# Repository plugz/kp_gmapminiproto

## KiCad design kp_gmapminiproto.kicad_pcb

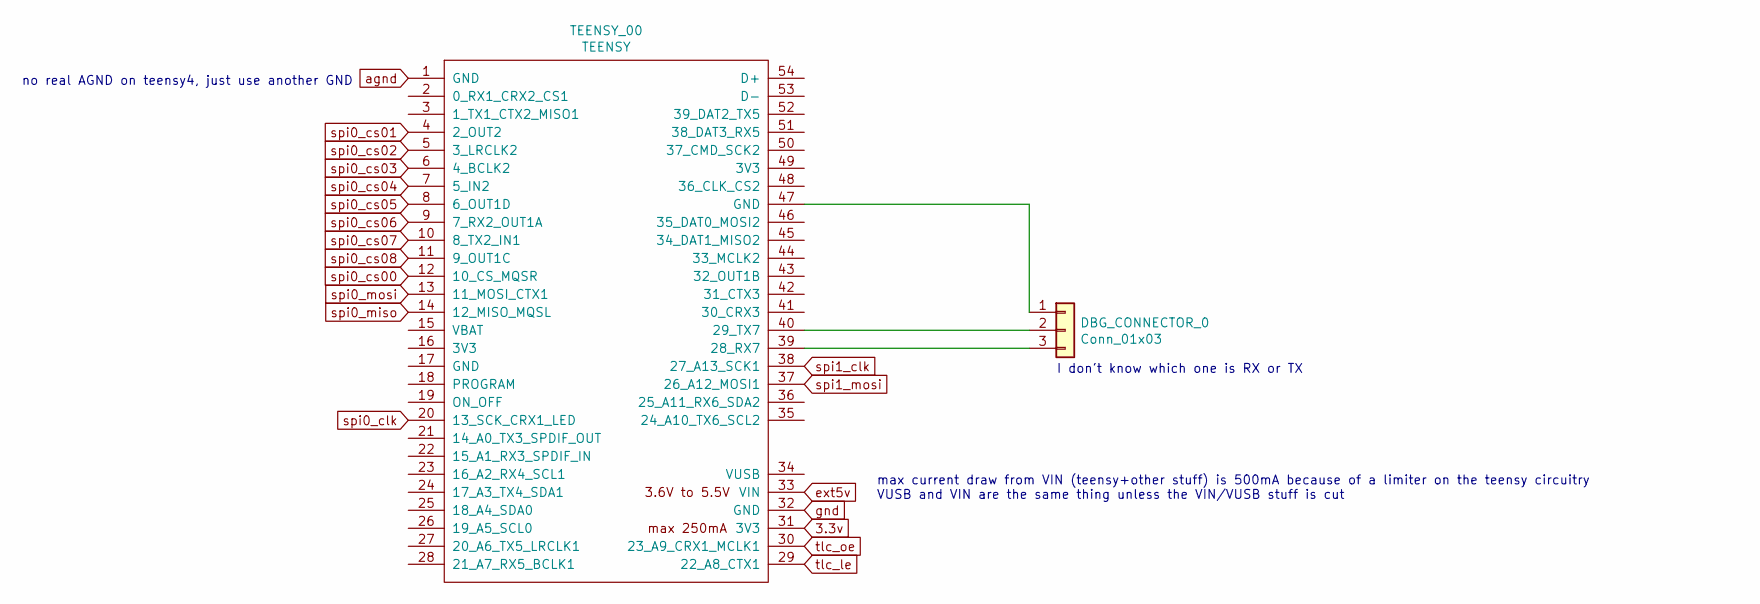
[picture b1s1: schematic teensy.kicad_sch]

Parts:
DBG_CONNECTOR_0: Conn_01x03; PinSocket_1x03_P2.54mm_Vertical
TEENSY_00: TEENSY; Teensy40_SMT

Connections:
3.3v: TEENSY_00.31 (3V3); also elsewhere on the board
unnamed: DBG_CONNECTOR_0.1, TEENSY_00.47 (GND)
unnamed: DBG_CONNECTOR_0.2, TEENSY_00.40 (29_TX7)
unnamed: DBG_CONNECTOR_0.3, TEENSY_00.39 (28_RX7)
agnd: TEENSY_00.1 (GND); also elsewhere on the board
ext5v: TEENSY_00.33 (VIN); also elsewhere on the board
gnd: TEENSY_00.32 (GND); also elsewhere on the board
spi0_clk: TEENSY_00.20 (13_SCK_CRX1_LED); also elsewhere on the board
spi0_cs00: TEENSY_00.12 (10_CS_MQSR); also elsewhere on the board
spi0_cs01: TEENSY_00.4 (2_OUT2); also elsewhere on the board
spi0_cs02: TEENSY_00.5 (3_LRCLK2); also elsewhere on the board
spi0_cs03: TEENSY_00.6 (4_BCLK2); also elsewhere on the board
spi0_cs04: TEENSY_00.7 (5_IN2); also elsewhere on the board
spi0_cs05: TEENSY_00.8 (6_OUT1D); also elsewhere on the board
spi0_cs06: TEENSY_00.9 (7_RX2_OUT1A); also elsewhere on the board
spi0_cs07: TEENSY_00.10 (8_TX2_IN1); also elsewhere on the board
spi0_cs08: TEENSY_00.11 (9_OUT1C); also elsewhere on the board
spi0_miso: TEENSY_00.14 (12_MISO_MQSL); also elsewhere on the board
spi0_mosi: TEENSY_00.13 (11_MOSI_CTX1); also elsewhere on the board
spi1_clk: TEENSY_00.38 (27_A13_SCK1); also elsewhere on the board
spi1_mosi: TEENSY_00.37 (26_A12_MOSI1); also elsewhere on the board
tlc_le: TEENSY_00.29 (22_A8_CTX1); also elsewhere on the board
tlc_oe: TEENSY_00.30 (23_A9_CRX1_MCLK1); also elsewhere on the board

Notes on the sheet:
max current draw from VIN (teensy+other stuff) is 500mA because of a limiter on the teensy circuitry VUSB and VIN are the same thing unless the VIN/VUSB stuff is cut
I don't know which one is RX or TX
no real AGND on teensy4, just use another GND

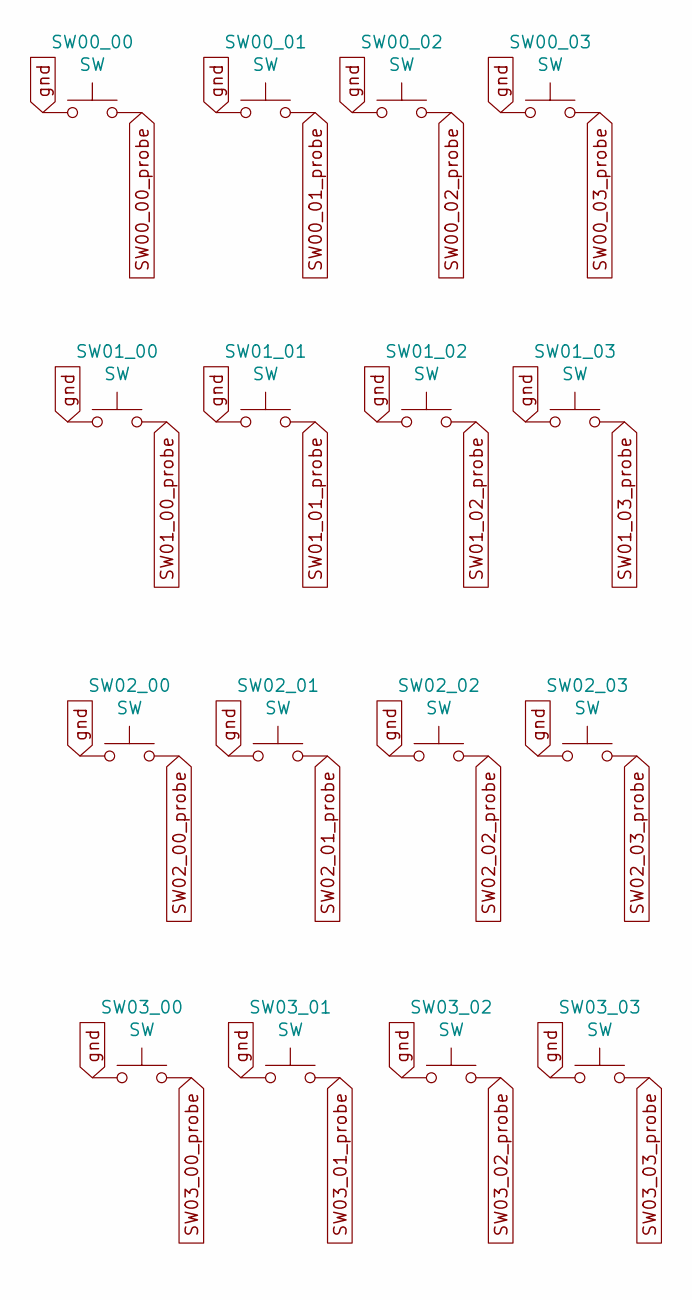
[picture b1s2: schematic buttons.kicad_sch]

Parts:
SW00_00, SW00_01, SW00_02, SW00_03, SW01_00, SW01_01, SW01_02, SW01_03, SW02_00, SW02_01, SW02_02, SW02_03, SW03_00, SW03_01, SW03_02, SW03_03: SW; SW_PUSH_6mm_h9.5mm

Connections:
SW00_00_probe: SW00_00.2; also elsewhere on the board
SW00_01_probe: SW00_01.2; also elsewhere on the board
SW00_02_probe: SW00_02.2; also elsewhere on the board
SW00_03_probe: SW00_03.2; also elsewhere on the board
SW01_00_probe: SW01_00.2; also elsewhere on the board
SW01_01_probe: SW01_01.2; also elsewhere on the board
SW01_02_probe: SW01_02.2; also elsewhere on the board
SW01_03_probe: SW01_03.2; also elsewhere on the board
SW02_00_probe: SW02_00.2; also elsewhere on the board
SW02_01_probe: SW02_01.2; also elsewhere on the board
SW02_02_probe: SW02_02.2; also elsewhere on the board
SW02_03_probe: SW02_03.2; also elsewhere on the board
SW03_00_probe: SW03_00.2; also elsewhere on the board
SW03_01_probe: SW03_01.2; also elsewhere on the board
SW03_02_probe: SW03_02.2; also elsewhere on the board
SW03_03_probe: SW03_03.2; also elsewhere on the board
gnd: SW00_00.1, SW00_01.1, SW00_02.1, SW00_03.1, SW01_00.1, SW01_01.1, SW01_02.1, SW01_03.1, SW02_00.1, SW02_01.1, SW02_02.1, SW02_03.1, SW03_00.1, SW03_01.1, SW03_02.1, SW03_03.1; also elsewhere on the board

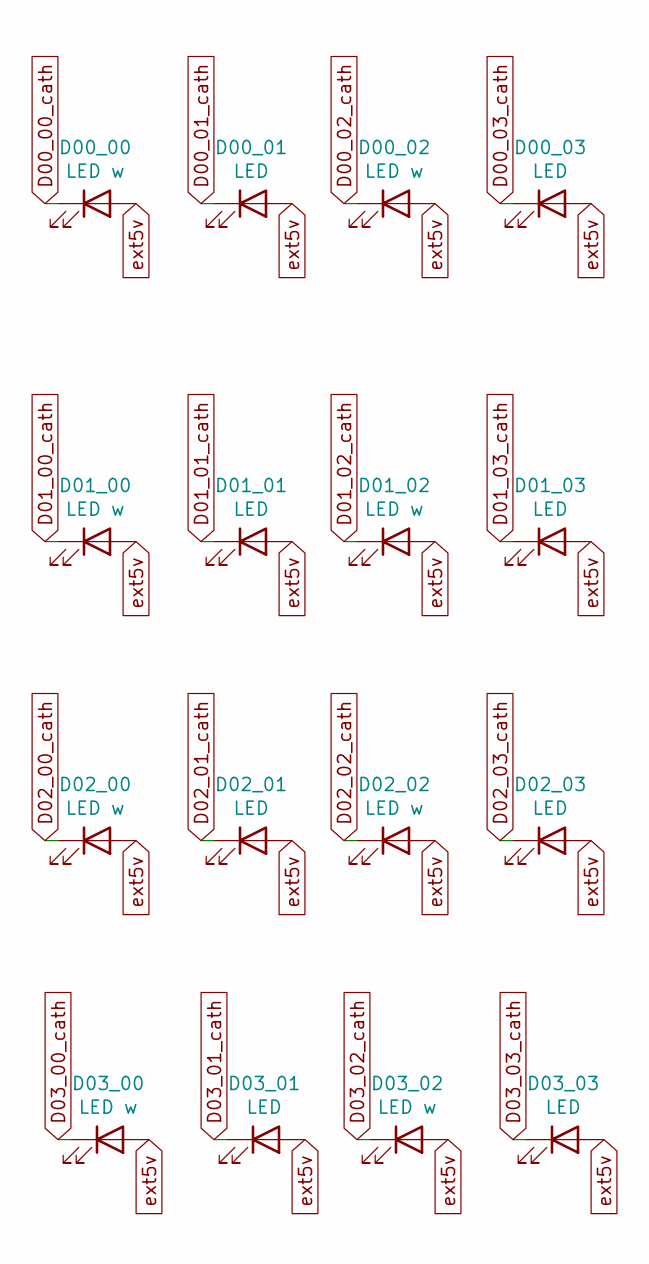
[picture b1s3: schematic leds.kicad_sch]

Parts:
D00_00, D00_02, D01_00, D01_02, D02_00, D02_02, D03_00, D03_02: LED w; LED_D3.0mm
D00_01, D00_03, D01_01, D01_03, D02_01, D02_03, D03_01, D03_03: LED; LED_D3.0mm

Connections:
D00_00_cath: D00_00.1 (K); also elsewhere on the board
D00_01_cath: D00_01.1 (K); also elsewhere on the board
D00_02_cath: D00_02.1 (K); also elsewhere on the board
D00_03_cath: D00_03.1 (K); also elsewhere on the board
D01_00_cath: D01_00.1 (K); also elsewhere on the board
D01_01_cath: D01_01.1 (K); also elsewhere on the board
D01_02_cath: D01_02.1 (K); also elsewhere on the board
D01_03_cath: D01_03.1 (K); also elsewhere on the board
D02_00_cath: D02_00.1 (K); also elsewhere on the board
D02_01_cath: D02_01.1 (K); also elsewhere on the board
D02_02_cath: D02_02.1 (K); also elsewhere on the board
D02_03_cath: D02_03.1 (K); also elsewhere on the board
D03_00_cath: D03_00.1 (K); also elsewhere on the board
D03_01_cath: D03_01.1 (K); also elsewhere on the board
D03_02_cath: D03_02.1 (K); also elsewhere on the board
D03_03_cath: D03_03.1 (K); also elsewhere on the board
ext5v: D00_00.2 (A), D00_01.2 (A), D00_02.2 (A), D00_03.2 (A), D01_00.2 (A), D01_01.2 (A), D01_02.2 (A), D01_03.2 (A), D02_00.2 (A), D02_01.2 (A), D02_02.2 (A), D02_03.2 (A), D03_00.2 (A), D03_01.2 (A), D03_02.2 (A), D03_03.2 (A); also elsewhere on the board

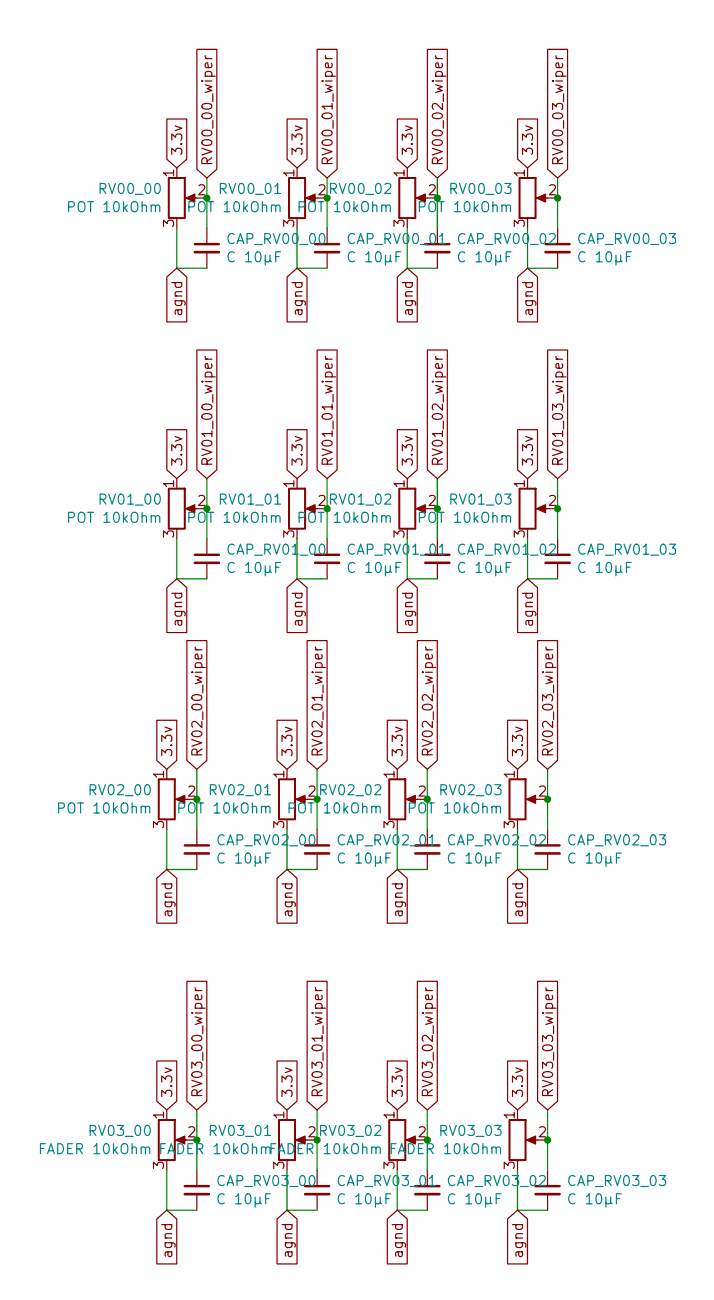
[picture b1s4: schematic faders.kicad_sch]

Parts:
CAP_RV00_00, CAP_RV00_01, CAP_RV00_02, CAP_RV00_03, CAP_RV01_00, CAP_RV01_01, CAP_RV01_02, CAP_RV01_03, CAP_RV02_00, CAP_RV02_01, CAP_RV02_02, CAP_RV02_03, CAP_RV03_00, CAP_RV03_01, CAP_RV03_02, CAP_RV03_03: C 10µF; C_Disc_D5.0mm_W2.5mm_P2.50mm
RV00_00, RV00_01, RV00_02, RV00_03, RV01_00, RV01_01, RV01_02, RV01_03, RV02_00, RV02_01, RV02_02, RV02_03: POT 10kOhm; Potentiometer_Alps_RK09K_Horizontal
RV03_00, RV03_01, RV03_02, RV03_03: FADER 10kOhm; Potentiometer_Bourns_PTA6043_Single_Slide

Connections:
3.3v: RV00_00.1, RV00_01.1, RV00_02.1, RV00_03.1, RV01_00.1, RV01_01.1, RV01_02.1, RV01_03.1, RV02_00.1, RV02_01.1, RV02_02.1, RV02_03.1, RV03_00.1, RV03_01.1, RV03_02.1, RV03_03.1; also elsewhere on the board
RV00_00_wiper: CAP_RV00_00.1, RV00_00.2; also elsewhere on the board
RV00_01_wiper: CAP_RV00_01.1, RV00_01.2; also elsewhere on the board
RV00_02_wiper: CAP_RV00_02.1, RV00_02.2; also elsewhere on the board
RV00_03_wiper: CAP_RV00_03.1, RV00_03.2; also elsewhere on the board
RV01_00_wiper: CAP_RV01_00.1, RV01_00.2; also elsewhere on the board
RV01_01_wiper: CAP_RV01_01.1, RV01_01.2; also elsewhere on the board
RV01_02_wiper: CAP_RV01_02.1, RV01_02.2; also elsewhere on the board
RV01_03_wiper: CAP_RV01_03.1, RV01_03.2; also elsewhere on the board
RV02_00_wiper: CAP_RV02_00.1, RV02_00.2; also elsewhere on the board
RV02_01_wiper: CAP_RV02_01.1, RV02_01.2; also elsewhere on the board
RV02_02_wiper: CAP_RV02_02.1, RV02_02.2; also elsewhere on the board
RV02_03_wiper: CAP_RV02_03.1, RV02_03.2; also elsewhere on the board
RV03_00_wiper: CAP_RV03_00.1, RV03_00.2; also elsewhere on the board
RV03_01_wiper: CAP_RV03_01.1, RV03_01.2; also elsewhere on the board
RV03_02_wiper: CAP_RV03_02.1, RV03_02.2; also elsewhere on the board
RV03_03_wiper: CAP_RV03_03.1, RV03_03.2; also elsewhere on the board
agnd: CAP_RV00_00.2, CAP_RV00_01.2, CAP_RV00_02.2, CAP_RV00_03.2, CAP_RV01_00.2, CAP_RV01_01.2, CAP_RV01_02.2, CAP_RV01_03.2, CAP_RV02_00.2, CAP_RV02_01.2, CAP_RV02_02.2, CAP_RV02_03.2, CAP_RV03_00.2, CAP_RV03_01.2, CAP_RV03_02.2, CAP_RV03_03.2, RV00_00.3, RV00_01.3, RV00_02.3, RV00_03.3, RV01_00.3, RV01_01.3, RV01_02.3, RV01_03.3, RV02_00.3, RV02_01.3, RV02_02.3, RV02_03.3, RV03_00.3, RV03_01.3, RV03_02.3, RV03_03.3; also elsewhere on the board

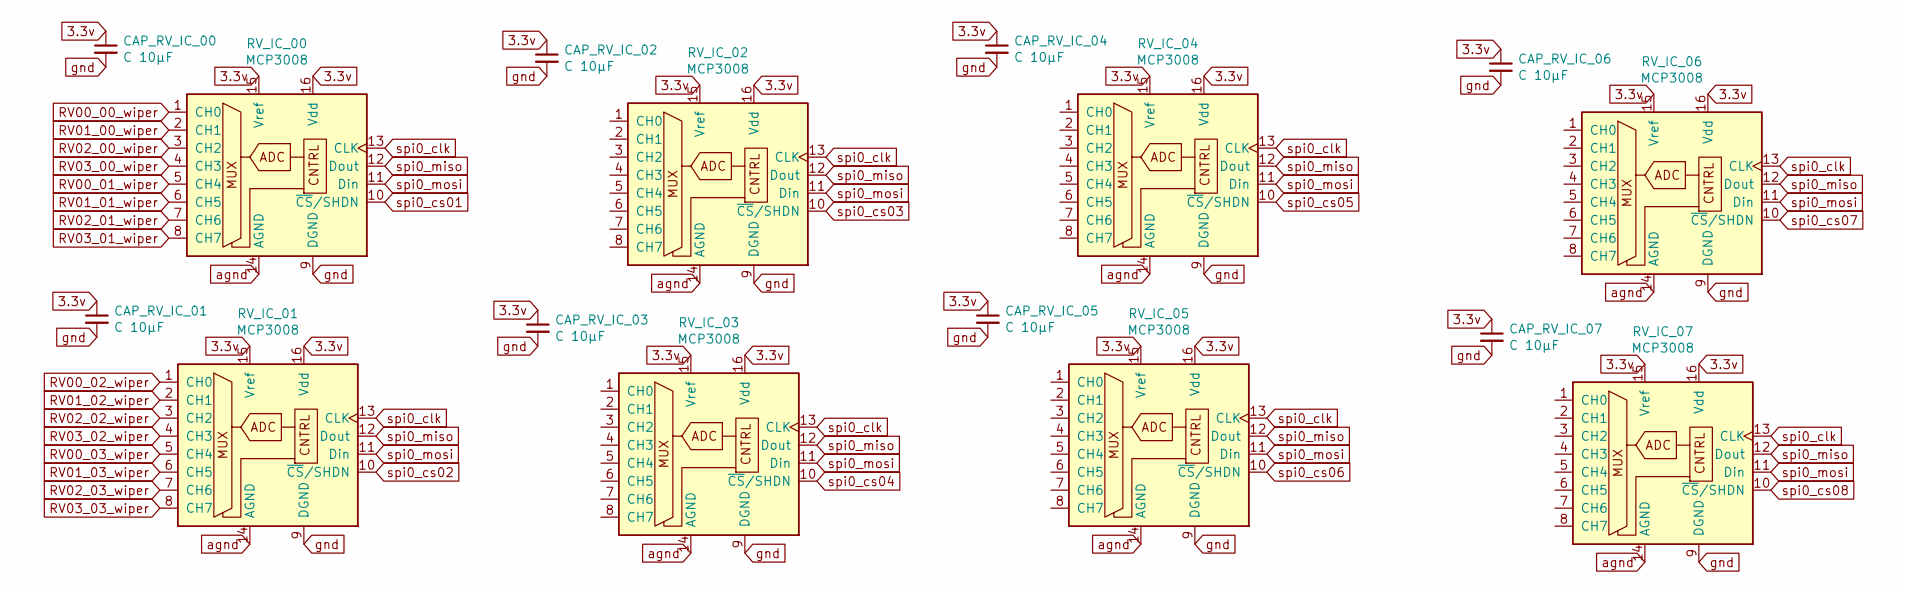
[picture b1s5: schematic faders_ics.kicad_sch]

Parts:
CAP_RV_IC_00, CAP_RV_IC_01, CAP_RV_IC_02, CAP_RV_IC_03, CAP_RV_IC_04, CAP_RV_IC_05, CAP_RV_IC_06, CAP_RV_IC_07: C 10µF; C_Disc_D5.0mm_W2.5mm_P2.50mm
RV_IC_00, RV_IC_01, RV_IC_02, RV_IC_03, RV_IC_04, RV_IC_05, RV_IC_06, RV_IC_07: MCP3008; DIP-16_W7.62mm

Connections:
3.3v: CAP_RV_IC_00.1, CAP_RV_IC_01.1, CAP_RV_IC_02.1, CAP_RV_IC_03.1, CAP_RV_IC_04.1, CAP_RV_IC_05.1, CAP_RV_IC_06.1, CAP_RV_IC_07.1, RV_IC_00.15 (Vref), RV_IC_00.16 (Vdd), RV_IC_01.15 (Vref), RV_IC_01.16 (Vdd), RV_IC_02.15 (Vref), RV_IC_02.16 (Vdd), RV_IC_03.15 (Vref), RV_IC_03.16 (Vdd), RV_IC_04.15 (Vref), RV_IC_04.16 (Vdd), RV_IC_05.15 (Vref), RV_IC_05.16 (Vdd), RV_IC_06.15 (Vref), RV_IC_06.16 (Vdd), RV_IC_07.15 (Vref), RV_IC_07.16 (Vdd); also elsewhere on the board
RV00_00_wiper: RV_IC_00.1 (CH0); also elsewhere on the board
RV00_01_wiper: RV_IC_00.5 (CH4); also elsewhere on the board
RV00_02_wiper: RV_IC_01.1 (CH0); also elsewhere on the board
RV00_03_wiper: RV_IC_01.5 (CH4); also elsewhere on the board
RV01_00_wiper: RV_IC_00.2 (CH1); also elsewhere on the board
RV01_01_wiper: RV_IC_00.6 (CH5); also elsewhere on the board
RV01_02_wiper: RV_IC_01.2 (CH1); also elsewhere on the board
RV01_03_wiper: RV_IC_01.6 (CH5); also elsewhere on the board
RV02_00_wiper: RV_IC_00.3 (CH2); also elsewhere on the board
RV02_01_wiper: RV_IC_00.7 (CH6); also elsewhere on the board
RV02_02_wiper: RV_IC_01.3 (CH2); also elsewhere on the board
RV02_03_wiper: RV_IC_01.7 (CH6); also elsewhere on the board
RV03_00_wiper: RV_IC_00.4 (CH3); also elsewhere on the board
RV03_01_wiper: RV_IC_00.8 (CH7); also elsewhere on the board
RV03_02_wiper: RV_IC_01.4 (CH3); also elsewhere on the board
RV03_03_wiper: RV_IC_01.8 (CH7); also elsewhere on the board
agnd: RV_IC_00.14 (AGND), RV_IC_01.14 (AGND), RV_IC_02.14 (AGND), RV_IC_03.14 (AGND), RV_IC_04.14 (AGND), RV_IC_05.14 (AGND), RV_IC_06.14 (AGND), RV_IC_07.14 (AGND); also elsewhere on the board
gnd: CAP_RV_IC_00.2, CAP_RV_IC_01.2, CAP_RV_IC_02.2, CAP_RV_IC_03.2, CAP_RV_IC_04.2, CAP_RV_IC_05.2, CAP_RV_IC_06.2, CAP_RV_IC_07.2, RV_IC_00.9 (DGND), RV_IC_01.9 (DGND), RV_IC_02.9 (DGND), RV_IC_03.9 (DGND), RV_IC_04.9 (DGND), RV_IC_05.9 (DGND), RV_IC_06.9 (DGND), RV_IC_07.9 (DGND); also elsewhere on the board
spi0_clk: RV_IC_00.13 (CLK), RV_IC_01.13 (CLK), RV_IC_02.13 (CLK), RV_IC_03.13 (CLK), RV_IC_04.13 (CLK), RV_IC_05.13 (CLK), RV_IC_06.13 (CLK), RV_IC_07.13 (CLK); also elsewhere on the board
spi0_cs01: RV_IC_00.10 (~CS/SHDN); also elsewhere on the board
spi0_cs02: RV_IC_01.10 (~CS/SHDN); also elsewhere on the board
spi0_cs03: RV_IC_02.10 (~CS/SHDN); also elsewhere on the board
spi0_cs04: RV_IC_03.10 (~CS/SHDN); also elsewhere on the board
spi0_cs05: RV_IC_04.10 (~CS/SHDN); also elsewhere on the board
spi0_cs06: RV_IC_05.10 (~CS/SHDN); also elsewhere on the board
spi0_cs07: RV_IC_06.10 (~CS/SHDN); also elsewhere on the board
spi0_cs08: RV_IC_07.10 (~CS/SHDN); also elsewhere on the board
spi0_miso: RV_IC_00.12 (Dout), RV_IC_01.12 (Dout), RV_IC_02.12 (Dout), RV_IC_03.12 (Dout), RV_IC_04.12 (Dout), RV_IC_05.12 (Dout), RV_IC_06.12 (Dout), RV_IC_07.12 (Dout); also elsewhere on the board
spi0_mosi: RV_IC_00.11 (Din), RV_IC_01.11 (Din), RV_IC_02.11 (Din), RV_IC_03.11 (Din), RV_IC_04.11 (Din), RV_IC_05.11 (Din), RV_IC_06.11 (Din), RV_IC_07.11 (Din); also elsewhere on the board

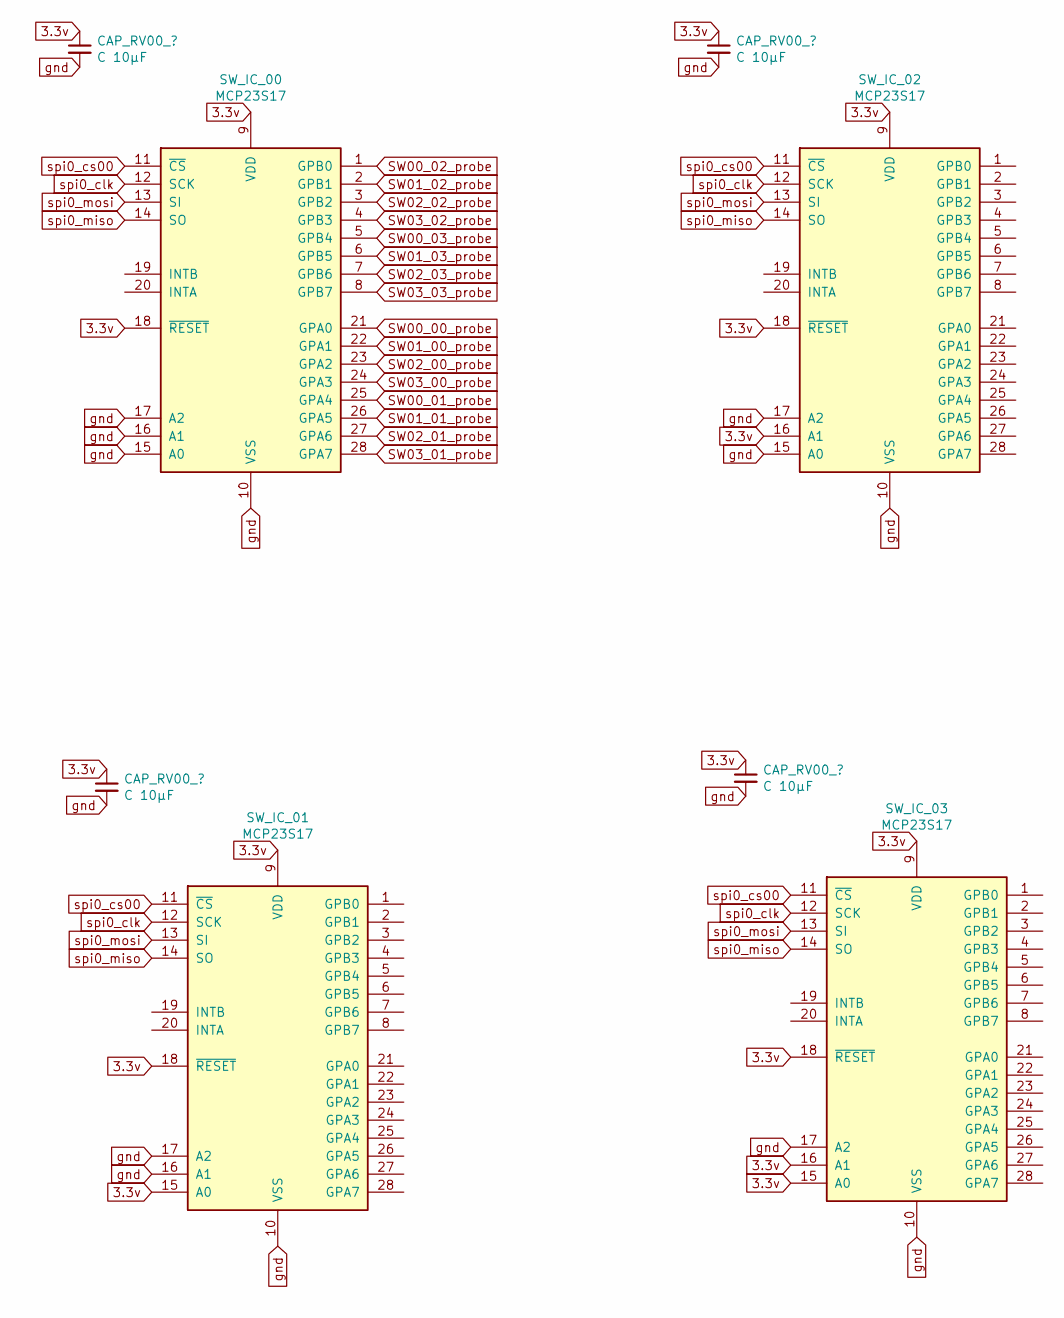
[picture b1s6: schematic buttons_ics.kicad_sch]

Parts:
CAP_SW_IC_00, CAP_SW_IC_01, CAP_SW_IC_02, CAP_SW_IC_03: C 10µF; C_Disc_D5.0mm_W2.5mm_P2.50mm
SW_IC_00, SW_IC_01, SW_IC_02, SW_IC_03: MCP23S17; DIP-28_W7.62mm

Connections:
3.3v: CAP_SW_IC_00.1, CAP_SW_IC_01.1, CAP_SW_IC_02.1, CAP_SW_IC_03.1, SW_IC_00.9 (VDD), SW_IC_00.18 (~RESET), SW_IC_01.9 (VDD), SW_IC_01.15 (A0), SW_IC_01.18 (~RESET), SW_IC_02.9 (VDD), SW_IC_02.16 (A1), SW_IC_02.18 (~RESET), SW_IC_03.9 (VDD), SW_IC_03.15 (A0), SW_IC_03.16 (A1), SW_IC_03.18 (~RESET); also elsewhere on the board
SW00_00_probe: SW_IC_00.21 (GPA0); also elsewhere on the board
SW00_01_probe: SW_IC_00.25 (GPA4); also elsewhere on the board
SW00_02_probe: SW_IC_00.1 (GPB0); also elsewhere on the board
SW00_03_probe: SW_IC_00.5 (GPB4); also elsewhere on the board
SW01_00_probe: SW_IC_00.22 (GPA1); also elsewhere on the board
SW01_01_probe: SW_IC_00.26 (GPA5); also elsewhere on the board
SW01_02_probe: SW_IC_00.2 (GPB1); also elsewhere on the board
SW01_03_probe: SW_IC_00.6 (GPB5); also elsewhere on the board
SW02_00_probe: SW_IC_00.23 (GPA2); also elsewhere on the board
SW02_01_probe: SW_IC_00.27 (GPA6); also elsewhere on the board
SW02_02_probe: SW_IC_00.3 (GPB2); also elsewhere on the board
SW02_03_probe: SW_IC_00.7 (GPB6); also elsewhere on the board
SW03_00_probe: SW_IC_00.24 (GPA3); also elsewhere on the board
SW03_01_probe: SW_IC_00.28 (GPA7); also elsewhere on the board
SW03_02_probe: SW_IC_00.4 (GPB3); also elsewhere on the board
SW03_03_probe: SW_IC_00.8 (GPB7); also elsewhere on the board
gnd: CAP_SW_IC_00.2, CAP_SW_IC_01.2, CAP_SW_IC_02.2, CAP_SW_IC_03.2, SW_IC_00.10 (VSS), SW_IC_00.15 (A0), SW_IC_00.16 (A1), SW_IC_00.17 (A2), SW_IC_01.10 (VSS), SW_IC_01.16 (A1), SW_IC_01.17 (A2), SW_IC_02.10 (VSS), SW_IC_02.15 (A0), SW_IC_02.17 (A2), SW_IC_03.10 (VSS), SW_IC_03.17 (A2); also elsewhere on the board
spi0_clk: SW_IC_00.12 (SCK), SW_IC_01.12 (SCK), SW_IC_02.12 (SCK), SW_IC_03.12 (SCK); also elsewhere on the board
spi0_cs00: SW_IC_00.11 (~CS), SW_IC_01.11 (~CS), SW_IC_02.11 (~CS), SW_IC_03.11 (~CS); also elsewhere on the board
spi0_miso: SW_IC_00.14 (SO), SW_IC_01.14 (SO), SW_IC_02.14 (SO), SW_IC_03.14 (SO); also elsewhere on the board
spi0_mosi: SW_IC_00.13 (SI), SW_IC_01.13 (SI), SW_IC_02.13 (SI), SW_IC_03.13 (SI); also elsewhere on the board

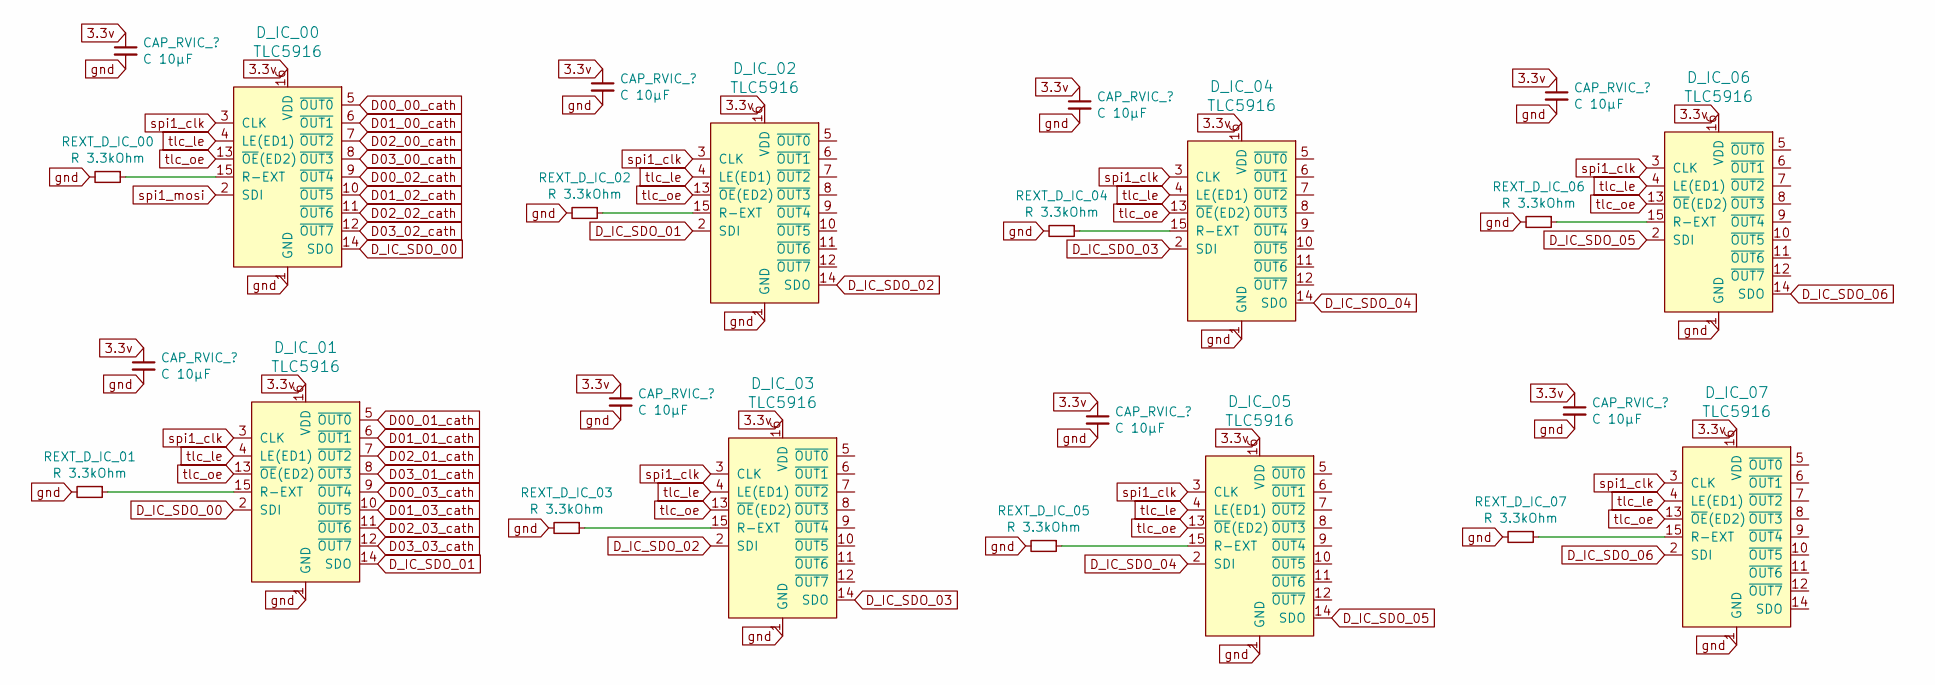
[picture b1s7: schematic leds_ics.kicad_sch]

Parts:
CAP_D_IC_00, CAP_D_IC_01, CAP_D_IC_02, CAP_D_IC_03, CAP_D_IC_04, CAP_D_IC_05, CAP_D_IC_06, CAP_D_IC_07: C 10µF; C_Disc_D5.0mm_W2.5mm_P2.50mm
D_IC_00, D_IC_01, D_IC_02, D_IC_03, D_IC_04, D_IC_05, D_IC_06, D_IC_07: TLC5916; DIP-16_W7.62mm; MPN TLC5916IN; Digi-Key_PN 296-24383-5-ND
REXT_D_IC_00, REXT_D_IC_01, REXT_D_IC_02, REXT_D_IC_03, REXT_D_IC_04, REXT_D_IC_05, REXT_D_IC_06, REXT_D_IC_07: R 3.3kOhm; R_Axial_DIN0207_L6.3mm_D2.5mm_P7.62mm_Horizontal

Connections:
3.3v: CAP_D_IC_00.1, CAP_D_IC_01.1, CAP_D_IC_02.1, CAP_D_IC_03.1, CAP_D_IC_04.1, CAP_D_IC_05.1, CAP_D_IC_06.1, CAP_D_IC_07.1, D_IC_00.16 (VDD), D_IC_01.16 (VDD), D_IC_02.16 (VDD), D_IC_03.16 (VDD), D_IC_04.16 (VDD), D_IC_05.16 (VDD), D_IC_06.16 (VDD), D_IC_07.16 (VDD); also elsewhere on the board
D00_00_cath: D_IC_00.5 (~OUT0); also elsewhere on the board
D00_01_cath: D_IC_01.5 (~OUT0); also elsewhere on the board
D00_02_cath: D_IC_00.9 (~OUT4); also elsewhere on the board
D00_03_cath: D_IC_01.9 (~OUT4); also elsewhere on the board
D01_00_cath: D_IC_00.6 (~OUT1); also elsewhere on the board
D01_01_cath: D_IC_01.6 (~OUT1); also elsewhere on the board
D01_02_cath: D_IC_00.10 (~OUT5); also elsewhere on the board
D01_03_cath: D_IC_01.10 (~OUT5); also elsewhere on the board
D02_00_cath: D_IC_00.7 (~OUT2); also elsewhere on the board
D02_01_cath: D_IC_01.7 (~OUT2); also elsewhere on the board
D02_02_cath: D_IC_00.11 (~OUT6); also elsewhere on the board
D02_03_cath: D_IC_01.11 (~OUT6); also elsewhere on the board
D03_00_cath: D_IC_00.8 (~OUT3); also elsewhere on the board
D03_01_cath: D_IC_01.8 (~OUT3); also elsewhere on the board
D03_02_cath: D_IC_00.12 (~OUT7); also elsewhere on the board
D03_03_cath: D_IC_01.12 (~OUT7); also elsewhere on the board
D_IC_SDO_00: D_IC_00.14 (SDO), D_IC_01.2 (SDI)
D_IC_SDO_01: D_IC_01.14 (SDO), D_IC_02.2 (SDI)
D_IC_SDO_02: D_IC_02.14 (SDO), D_IC_03.2 (SDI)
D_IC_SDO_03: D_IC_03.14 (SDO), D_IC_04.2 (SDI)
D_IC_SDO_04: D_IC_04.14 (SDO), D_IC_05.2 (SDI)
D_IC_SDO_05: D_IC_05.14 (SDO), D_IC_06.2 (SDI)
D_IC_SDO_06: D_IC_06.14 (SDO), D_IC_07.2 (SDI)
unnamed: D_IC_00.15 (R-EXT), REXT_D_IC_00.1
unnamed: D_IC_01.15 (R-EXT), REXT_D_IC_01.1
unnamed: D_IC_02.15 (R-EXT), REXT_D_IC_02.1
unnamed: D_IC_03.15 (R-EXT), REXT_D_IC_03.1
unnamed: D_IC_04.15 (R-EXT), REXT_D_IC_04.1
unnamed: D_IC_05.15 (R-EXT), REXT_D_IC_05.1
unnamed: D_IC_06.15 (R-EXT), REXT_D_IC_06.1
unnamed: D_IC_07.15 (R-EXT), REXT_D_IC_07.1
gnd: CAP_D_IC_00.2, CAP_D_IC_01.2, CAP_D_IC_02.2, CAP_D_IC_03.2, CAP_D_IC_04.2, CAP_D_IC_05.2, CAP_D_IC_06.2, CAP_D_IC_07.2, D_IC_00.1 (GND), D_IC_01.1 (GND), D_IC_02.1 (GND), D_IC_03.1 (GND), D_IC_04.1 (GND), D_IC_05.1 (GND), D_IC_06.1 (GND), D_IC_07.1 (GND), REXT_D_IC_00.2, REXT_D_IC_01.2, REXT_D_IC_02.2, REXT_D_IC_03.2, REXT_D_IC_04.2, REXT_D_IC_05.2, REXT_D_IC_06.2, REXT_D_IC_07.2; also elsewhere on the board
spi1_clk: D_IC_00.3 (CLK), D_IC_01.3 (CLK), D_IC_02.3 (CLK), D_IC_03.3 (CLK), D_IC_04.3 (CLK), D_IC_05.3 (CLK), D_IC_06.3 (CLK), D_IC_07.3 (CLK); also elsewhere on the board
spi1_mosi: D_IC_00.2 (SDI); also elsewhere on the board
tlc_le: D_IC_00.4 (LE(ED1)), D_IC_01.4 (LE(ED1)), D_IC_02.4 (LE(ED1)), D_IC_03.4 (LE(ED1)), D_IC_04.4 (LE(ED1)), D_IC_05.4 (LE(ED1)), D_IC_06.4 (LE(ED1)), D_IC_07.4 (LE(ED1)); also elsewhere on the board
tlc_oe: D_IC_00.13 (~OE(ED2)), D_IC_01.13 (~OE(ED2)), D_IC_02.13 (~OE(ED2)), D_IC_03.13 (~OE(ED2)), D_IC_04.13 (~OE(ED2)), D_IC_05.13 (~OE(ED2)), D_IC_06.13 (~OE(ED2)), D_IC_07.13 (~OE(ED2)); also elsewhere on the board

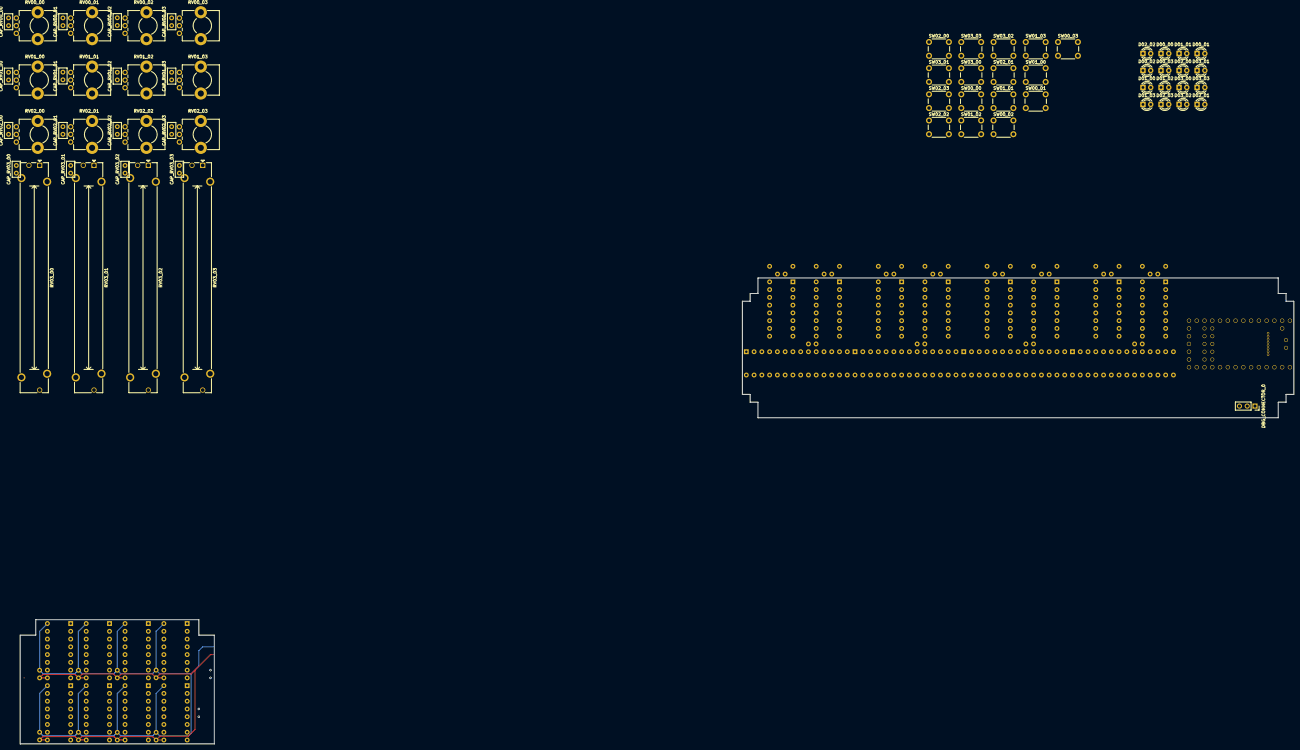
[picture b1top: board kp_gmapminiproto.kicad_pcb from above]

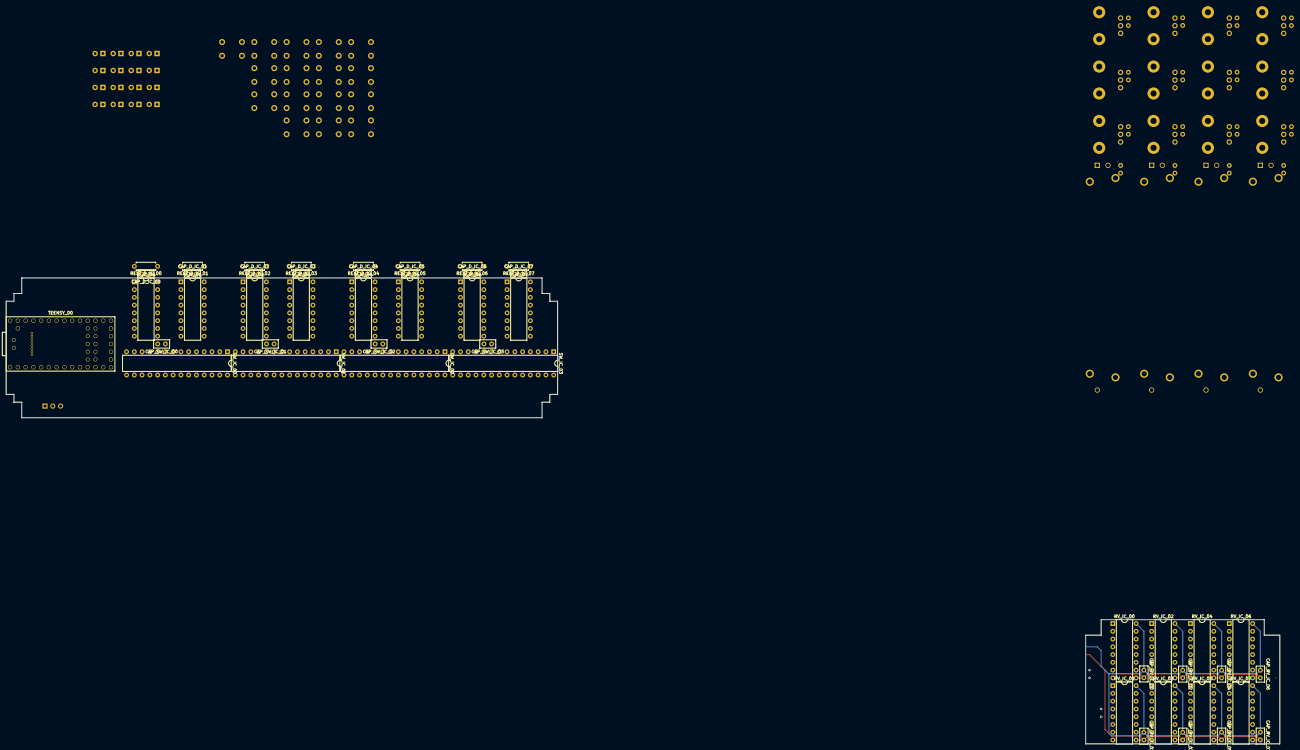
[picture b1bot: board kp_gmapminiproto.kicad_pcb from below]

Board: 10 copper layers, 114 parts (49 on the bottom side), 86 nets.

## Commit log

2020-05-26 init commit
2020-05-26 add files
2023-08-11 update for kicad 7
